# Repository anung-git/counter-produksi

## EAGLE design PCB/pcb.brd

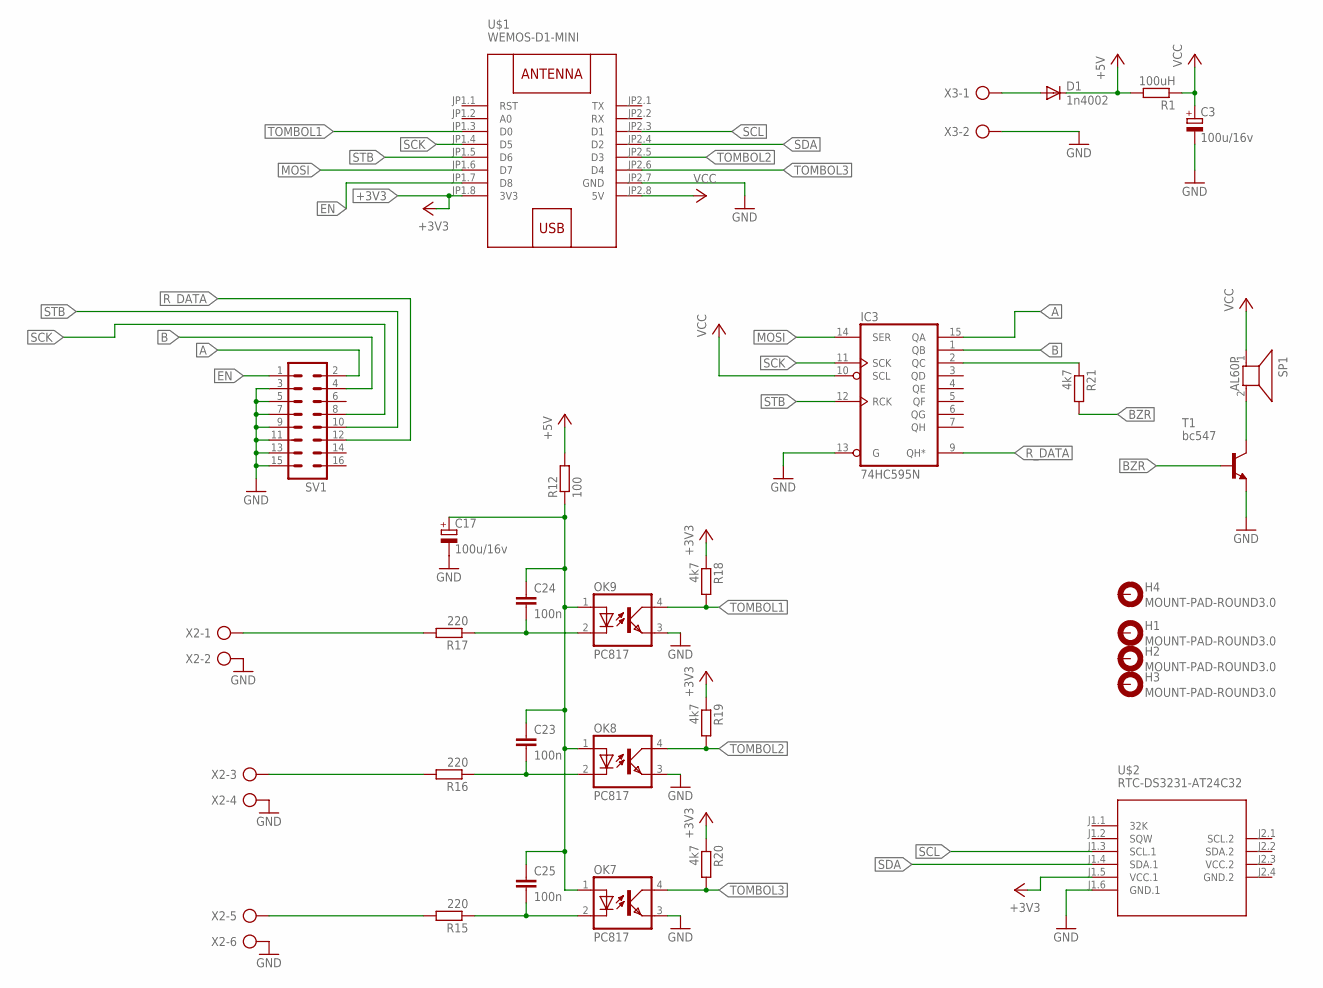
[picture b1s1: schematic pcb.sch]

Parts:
C3, C17: 100u/16v; E5-4
C23, C24, C25: 100n; C050-025X075
D1: 1n4002; DO35-10
H1, H2, H3, H4: MOUNT-PAD-ROUND3.0; 3,0-PAD
IC3: 74HC595N; DIL16
OK7, OK8, OK9: PC817; DIL04
R1: 100uH; 0207/10
R12: 100; 0207/10
R15, R16, R17: 220; 0207/10
R18, R19, R20, R21: 4k7; 0207/10
SP1: AL60P
SV1: ML16
T1: bc547; TO92-CBE
U$1: WEMOS-D1-MINI
U$2: RTC-DS3231-AT24C32
X2: AK300/6
X3: AK300/2

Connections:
+3V3: R18.1, R19.1, R20.1, U$1.JP1.8 (3V3), U$2.J1.5 (VCC.1)
+5V: D1.C, R1.2, R12.2
A: IC3.15 (QA), SV1.2
B: IC3.1 (QB), SV1.4
BZR: R21.2, T1.B
EN: SV1.1, U$1.JP1.7 (D8)
GND: C3.-, C17.-, IC3.8 (GND), IC3.13 (G), OK7.3 (EMIT), OK8.3 (EMIT), OK9.3 (EMIT), SV1.3, SV1.5, SV1.7, SV1.9, SV1.11, SV1.13, SV1.15, T1.E, U$1.JP2.7 (GND), U$2.J1.6 (GND.1), X2.2, X2.4, X2.6, X3.2
GND.2: U$2.J2.4 (GND.2)
MOSI: IC3.14 (SER), U$1.JP1.6 (D7)
unnamed: SP1.2, T1.C
unnamed: D1.A, X3.1
unnamed: C24.2, OK9.2 (C), R17.1
unnamed: C25.2, OK7.2 (C), R15.1
unnamed: C23.2, OK8.2 (C), R16.1
unnamed: R15.2, X2.5
unnamed: R16.2, X2.3
unnamed: R17.2, X2.1
unnamed: C17.+, C23.1, C24.1, C25.1, OK7.1 (A), OK8.1 (A), OK9.1 (A), R12.1
unnamed: IC3.2 (QC), R21.1
R_DATA: IC3.9 (QH*), SV1.12
SCK: IC3.11 (SCK), SV1.8, U$1.JP1.4 (D5)
SCL: U$1.JP2.3 (D1), U$2.J1.3 (SCL.1)
SDA: U$1.JP2.4 (D2), U$2.J1.4 (SDA.1)
STB: IC3.12 (RCK), SV1.10, U$1.JP1.5 (D6)
TOMBOL1: OK9.4 (COL), R18.2, U$1.JP1.3 (D0)
TOMBOL2: OK8.4 (COL), R19.2, U$1.JP2.5 (D3)
TOMBOL3: OK7.4 (COL), R20.2, U$1.JP2.6 (D4)
VCC: C3.+, IC3.10 (SCL), IC3.16 (VCC), R1.1, SP1.1, U$1.JP2.8 (5V)
VCC.2: U$2.J2.3 (VCC.2)

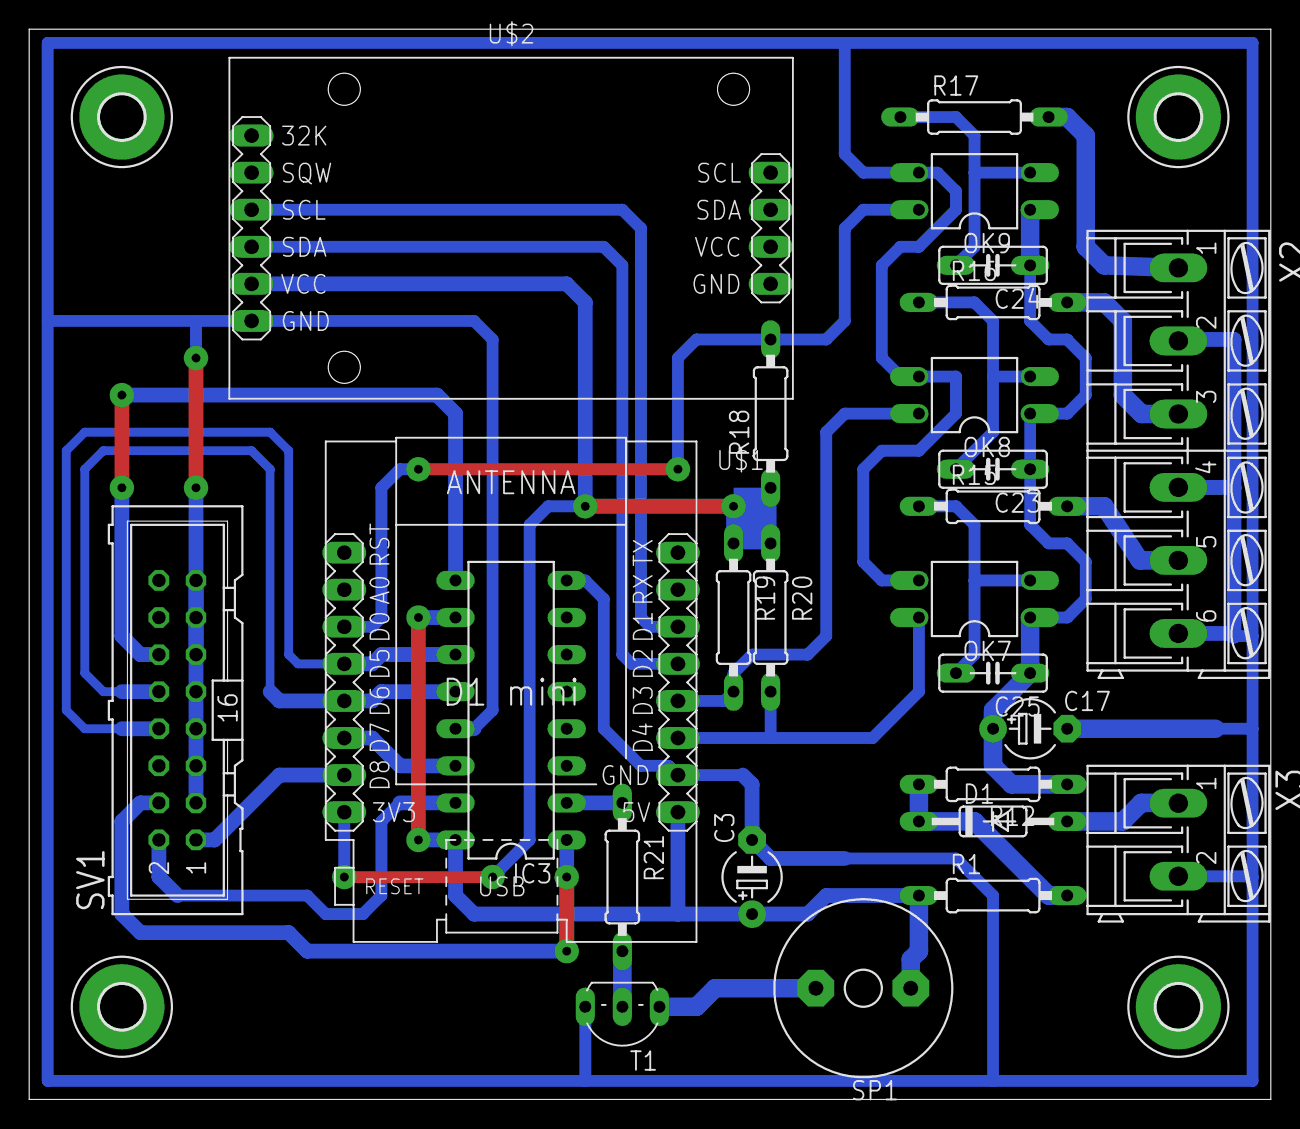
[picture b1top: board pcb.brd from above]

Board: 2 copper layers, 85.1 x 73.3 mm, 30 parts (0 on the bottom side), 27 nets.

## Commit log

2021-01-09 upload

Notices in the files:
parts and their libraries:
diy-modules: Released under the Creative Commons Attribution 4.0 International License: http://creativecommons.org/licenses/by/4.0
